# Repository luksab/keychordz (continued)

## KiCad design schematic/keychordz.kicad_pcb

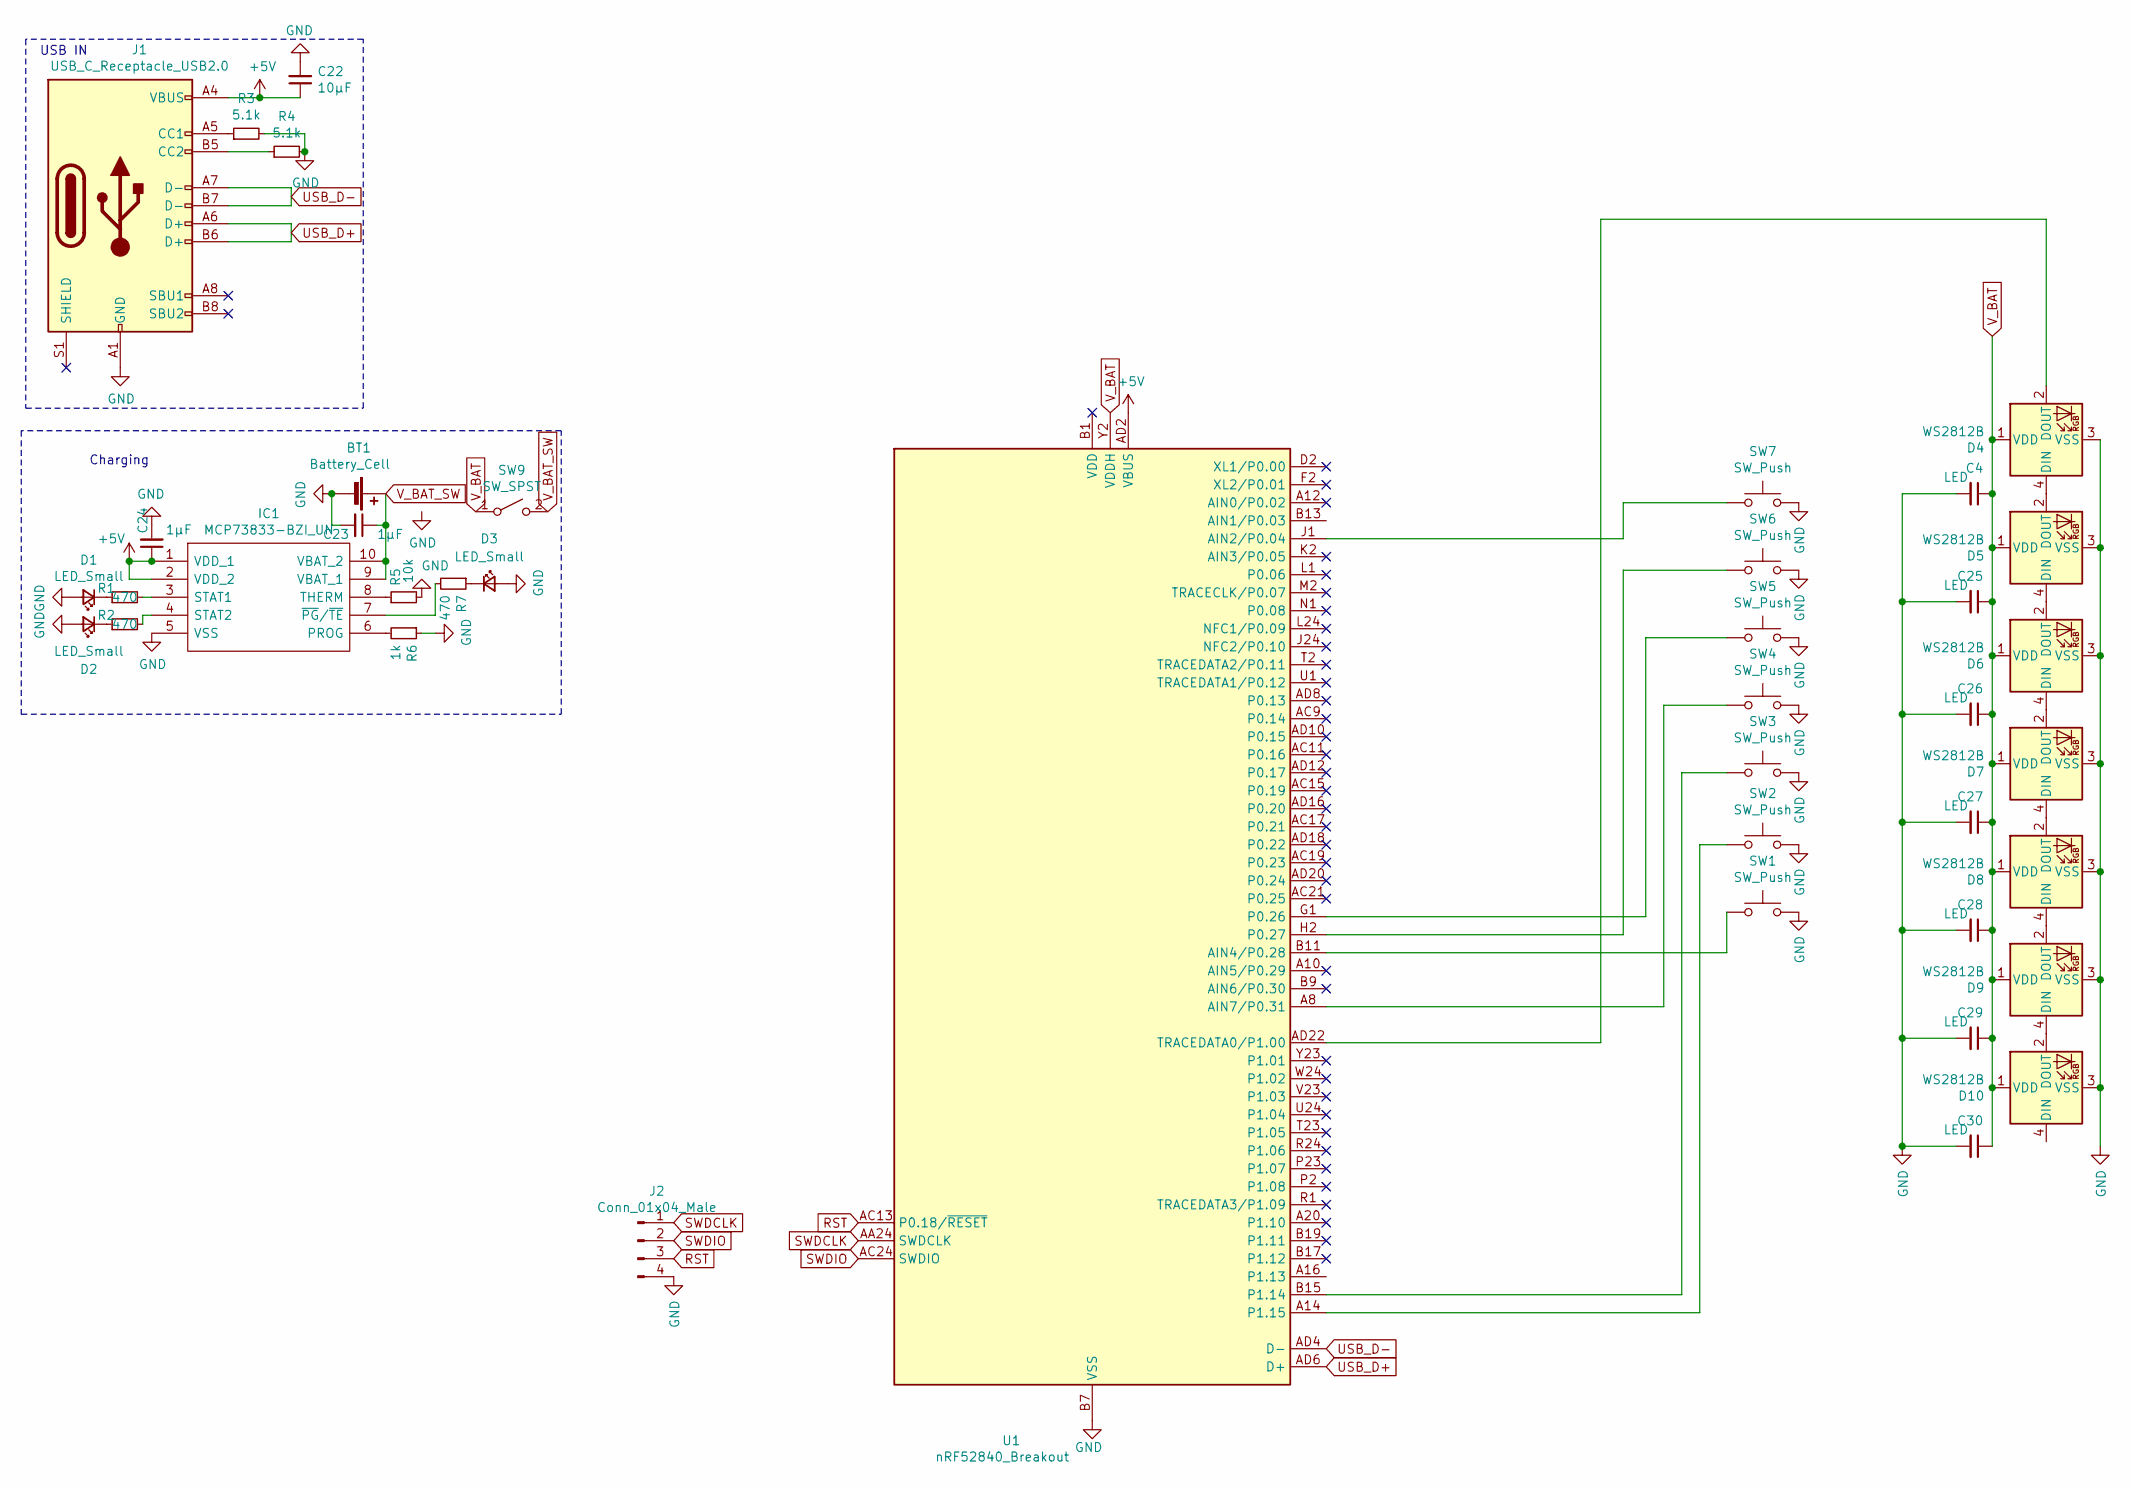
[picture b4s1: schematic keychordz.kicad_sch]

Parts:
BT1: Battery_Cell; BatteryHolder_MPD_BH-18650-PC2
C4, C25, C26, C27, C28, C29, C30: LED; C_0603_1608Metric_Pad1.08x0.95mm_HandSolder
C22: 10µF; C_0805_2012Metric_Pad1.18x1.45mm_HandSolder
C23, C24: 1µF; C_0402_1005Metric_Pad0.74x0.62mm_HandSolder
D1, D2, D3: LED_Small; LED_0603_1608Metric_Pad1.05x0.95mm_HandSolder
D4, D5, D6, D7, D8, D9, D10: WS2812B; LED_WS2812B_PLCC4_2.2x2.2mm
IC1: MCP73833-BZI_UN; MSOP-10_3x3mm_P0.5mm; Mouser Part Number 579-MCP73833-BZI/UN
J1: USB_C_Receptacle_USB2.0; USB_C_Receptacle_Amphenol_12401548E4-2A
J2: Conn_01x04_Male; PinHeader_1x04_P2.54mm_Vertical
R1, R2, R7: 470; R_0603_1608Metric_Pad0.98x0.95mm_HandSolder
R3, R4: 5.1k; R_0603_1608Metric_Pad0.98x0.95mm_HandSolder
R5: 10k; R_0402_1005Metric_Pad0.72x0.64mm_HandSolder
R6: 1k; R_0402_1005Metric_Pad0.72x0.64mm_HandSolder
SW1, SW2, SW3, SW4, SW5, SW6, SW7: SW_Push; SW_PG1350
SW9: SW_SPST; SW_DIP_SPSTx02_Slide_6.7x6.64mm_W7.62mm_P2.54mm_LowProfile
U1: nRF52840_Breakout

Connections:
+5V: C22.1, C24.1, IC1.1 (VDD_1), IC1.2 (VDD_2), J1.A4 (VBUS), U1.AD2 (VBUS)
GND: BT1.2 (-), C4.2, C22.2, C23.2, C24.2, C25.2, C26.2, C27.2, C28.2, C29.2, C30.2, D1.2 (A), D2.2 (A), D3.2 (A), D4.3 (VSS), D5.3 (VSS), D6.3 (VSS), D7.3 (VSS), D8.3 (VSS), D9.3 (VSS), D10.3 (VSS), IC1.5 (VSS), J1.A1 (GND), J2.4, R3.2, R4.2, R5.2, R6.1, SW1.2, SW2.2, SW3.2, SW4.2, SW5.2, SW6.2, SW7.2, U1.B7 (VSS); also elsewhere on the board
unnamed: D1.1 (K), R1.1
unnamed: D2.1 (K), R2.1
unnamed: D3.1 (K), R7.1
unnamed: D4.2 (DOUT), U1.AD22 (TRACEDATA0/P1.00)
unnamed: D4.4 (DIN), D5.2 (DOUT)
unnamed: D5.4 (DIN), D6.2 (DOUT)
unnamed: D6.4 (DIN), D7.2 (DOUT)
unnamed: D7.4 (DIN), D8.2 (DOUT)
unnamed: D8.4 (DIN), D9.2 (DOUT)
unnamed: D9.4 (DIN), D10.2 (DOUT)
unnamed: IC1.3 (STAT1), R1.2
unnamed: IC1.4 (STAT2), R2.2
unnamed: IC1.6 (PROG), R6.2
unnamed: IC1.7 (~PG~/~TE), R7.2
unnamed: IC1.8 (THERM), R5.1
unnamed: J1.A5 (CC1), R3.1
unnamed: J1.B5 (CC2), R4.1
unnamed 19: U1.B1 (VDD); also elsewhere on the board
unnamed 20: U1.L1 (P0.06); also elsewhere on the board
unnamed: SW1.1, U1.B11 (AIN4/P0.28)
unnamed: SW2.1, U1.A14 (P1.15)
unnamed: SW3.1, U1.B15 (P1.14)
unnamed: SW4.1, U1.A8 (AIN7/P0.31)
unnamed: SW5.1, U1.G1 (P0.26)
unnamed: SW6.1, U1.H2 (P0.27)
unnamed: SW7.1, U1.J1 (AIN2/P0.04)
unnamed 28: U1.K2 (AIN3/P0.05); also elsewhere on the board
unnamed 29: U1.M2 (TRACECLK/P0.07); also elsewhere on the board
unnamed 30: U1.N1 (P0.08); also elsewhere on the board
unnamed 31: U1.P2 (P1.08); also elsewhere on the board
RST: J2.3, U1.AC13 (P0.18/~RESET)
SWDCLK: J2.1, U1.AA24 (SWDCLK)
SWDIO: J2.2, U1.AC24 (SWDIO)
USB_D+: J1.A6 (D+), J1.B6 (D+), U1.AD6 (D+)
USB_D-: J1.A7 (D-), J1.B7 (D-), U1.AD4 (D-)
V_BAT: C4.1, C25.1, C26.1, C27.1, C28.1, C29.1, C30.1, D4.1 (VDD), D5.1 (VDD), D6.1 (VDD), D7.1 (VDD), D8.1 (VDD), D9.1 (VDD), D10.1 (VDD), SW9.1 (A), U1.Y2 (VDDH)
V_BAT_SW: BT1.1 (+), C23.1, IC1.9 (VBAT_1), IC1.10 (VBAT_2), SW9.2 (B)

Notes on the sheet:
USB IN
Charging

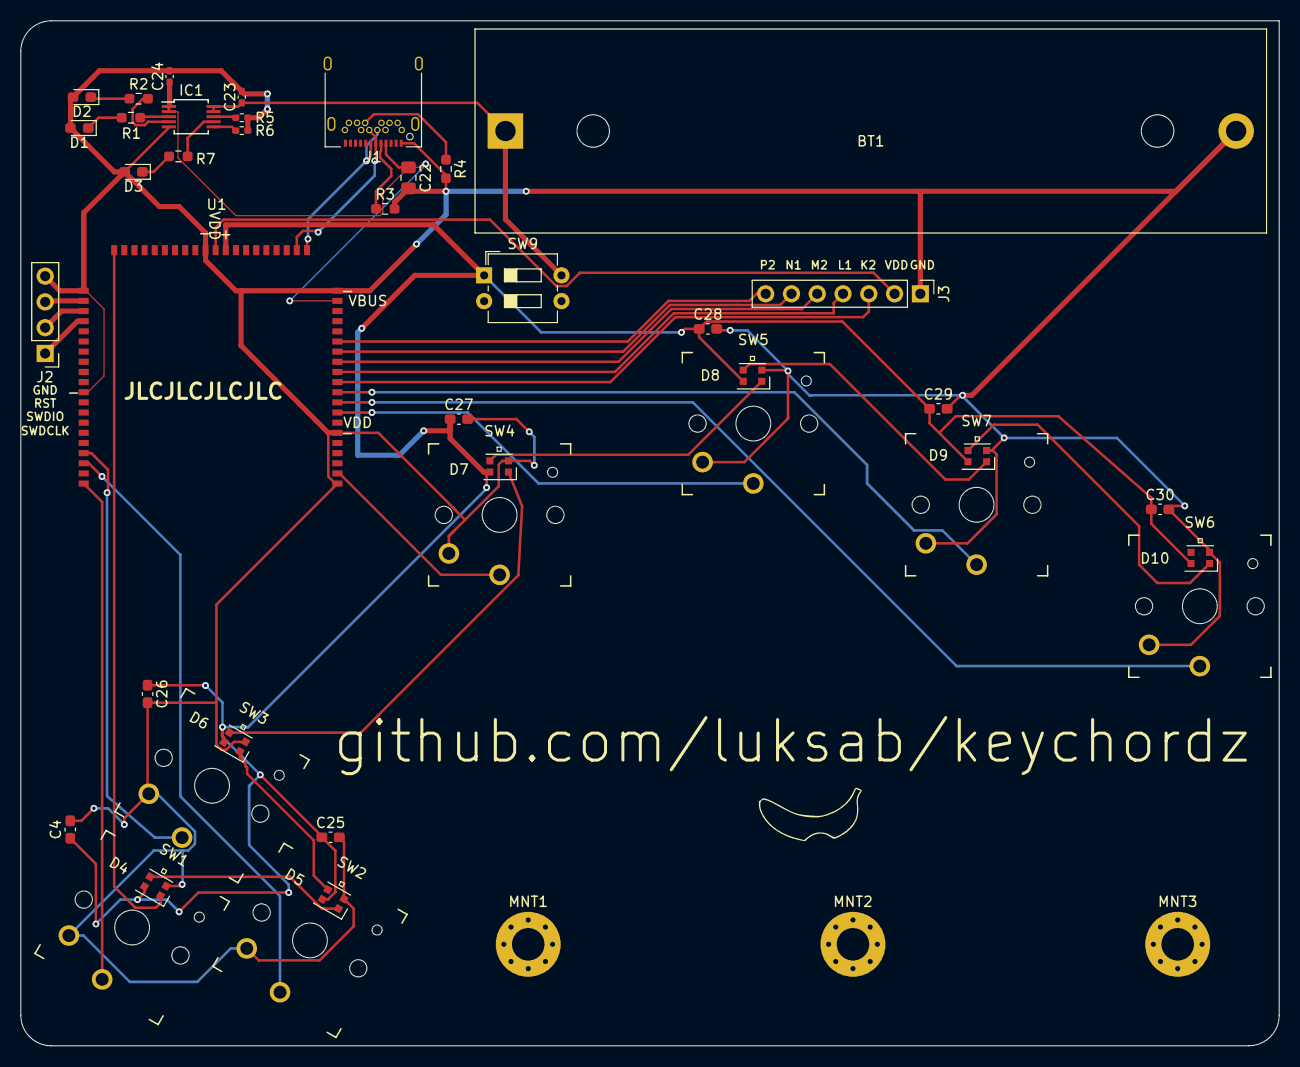
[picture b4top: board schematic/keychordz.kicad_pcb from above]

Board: 2 copper layers, 124.0 x 101.0 mm, 44 parts (0 on the bottom side), 39 nets.

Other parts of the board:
J3: Conn_01x04_Male; PinHeader_1x07_P2.54mm_Vertical
MNT1, MNT2, MNT3: MountingHole_3.2mm_M3_Pad_Via

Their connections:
GND: J3.1; also elsewhere on the board
unnamed 19: J3.2; also elsewhere on the board
unnamed 20: J3.4; also elsewhere on the board
unnamed 28: J3.3; also elsewhere on the board
unnamed 29: J3.5; also elsewhere on the board
unnamed 30: J3.6; also elsewhere on the board
unnamed 31: J3.7; also elsewhere on the board

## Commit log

2021-02-23 init
2021-03-02 schematic first version
2021-03-06 add Breakout
2021-03-07 keyboard schematic with breakout
2021-03-08 update breakout without castellations
2021-03-09 finish up Schematics
2021-03-13 change left PCB to STM32
2021-03-13 change right PCB to STM32
2021-03-13 change OLED voltage to V_BAT (ordered this commit)
2022-04-08 use Arduino pro micro
2022-04-08 fix LED vcc
2022-04-09 init qmk
2022-04-09 compiling qmk firmware
2022-04-09 add readme to qmk
2022-04-11 use pin hand detection
2022-04-15 Add link to readme
2022-04-15 add keycap stl
2022-04-15 update keymap ascii art with numers
2022-04-15 enable combos
2022-04-16 add keystats
2022-04-16 use walkdir for orders of magnitude better perf
2022-04-16 add more stats
2022-04-16 start with doubles
2022-04-19 add cmd options
2022-04-19 use hashmaps to allow any n
2022-04-19 clean up code
2022-04-19 multithread analysis
2022-04-21 improve output
2022-04-25 add rgb and first combos
2022-04-25 add (incomplete) parser
2022-04-25 allow empty lines and lower case in cfg
2022-04-25 first combo output
2022-04-25 fix output
2022-04-25 allow keycodes
2022-04-25 full asetniop layout
2022-05-05 init firmware
2022-05-06 working protocol
2022-05-06 include atmega32u4-usb-hid in repo
2022-05-06 ws2812 bit banging
2022-05-07 add basic led lib
2022-05-07 add (inefficient) "gamma" to led
2022-05-07 add key press check
2022-05-08 remove some nops
2022-05-08 docs
2022-05-09 make AlreadyRunning error the same for read/write
2022-05-09 add pins.md lookup table
2022-05-09 add key_state
2022-05-09 don't double define __AVR_ATmega32U4__
2022-05-10 format cargo.toml
2022-05-10 longer atomics
2022-05-10 add libcAllcator
2022-05-10 default to 50 brightness
2022-05-10 add EEPROM
2022-05-10 add key_handler
2022-05-11 move defines to their own crate
2022-05-11 working asetniop layout
2022-05-11 sort keys beforehand to save ~5k progmem
2022-05-11 repr u8 just to be sure
2022-05-12 update toolchain and edition
2022-05-13 adjust chocCap
2022-05-13 optimize led further
2022-05-16 add readme
2022-05-19 add new hardware rev
2022-05-20 add backside and rounded corners
2022-05-20 start routing
2022-05-21 finish routing
2022-05-23 oder V3
2022-06-01 update readme for firmware
2022-06-03 add eeprom struct functions
2022-06-03 add ufmt to defines
2022-06-03 add global print
2022-06-03 add better error to eeprom
